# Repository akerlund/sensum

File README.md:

# sensum
Project with many different sensors

Using ChibiOS and so far this is not complete at all.

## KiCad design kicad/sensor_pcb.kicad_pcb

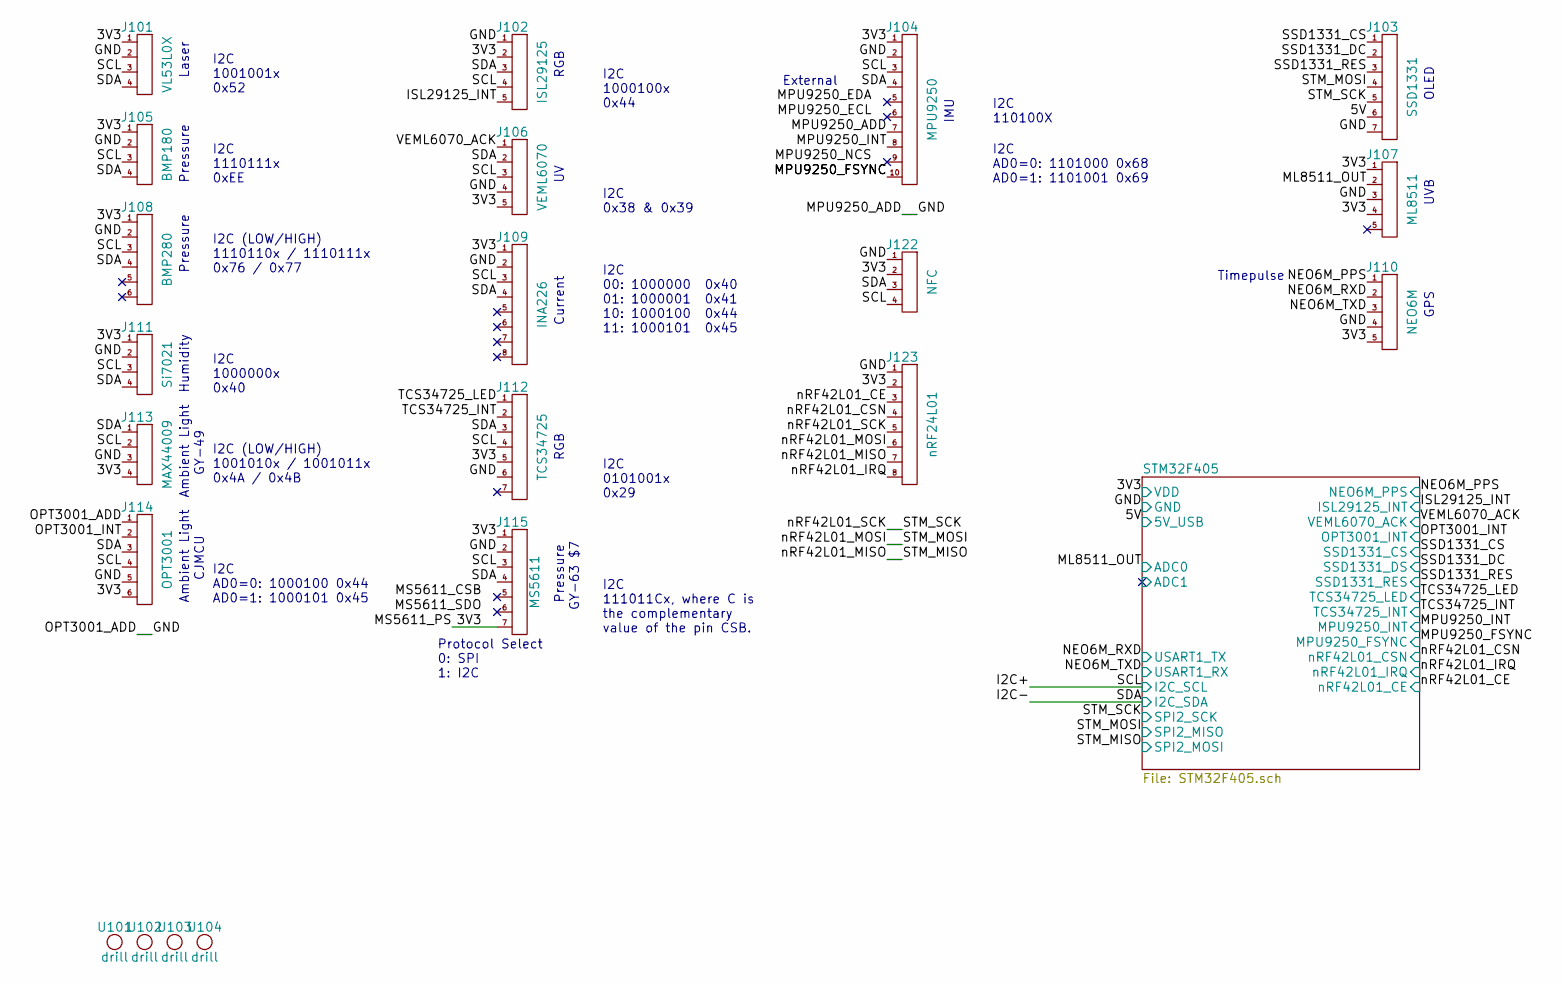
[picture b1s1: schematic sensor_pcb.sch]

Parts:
J101: VL53L0X; pin_socket_4
J102: ISL29125; pin_socket_5
J103: SSD1331; pin_socket_7
J104: MPU9250; pin_socket_10
J105: BMP180; pin_socket_4
J106: VEML6070; pin_socket_5
J107: ML8511; pin_strip_5
J108: BMP280; pin_strip_6
J109: INA226; pin_socket_8
J110: NEO6M; pin_socket_5
J111: Si7021; pin_socket_4
J112: TCS34725; pin_socket_7
J113: MAX44009; pin_socket_4
J114: OPT3001; pin_socket_6
J115: MS5611; pin_socket_7
J122: NFC; pin_socket_4
J123: nRF24L01; pin_socket_4x2
U101, U102, U103, U104: drill; drill_2.0mm

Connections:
/3V3: J101.1, J102.2, J104.1, J105.1, J106.5, J107.1, J107.4, J108.1, J109.1, J110.5, J111.1, J112.5, J113.4, J114.6, J115.1, J115.7, J122.2, J123.2; also elsewhere on the board
/5V: J103.6; also elsewhere on the board
/GND: J101.2, J102.1, J103.7, J104.2, J104.7, J105.2, J106.4, J107.3, J108.2, J109.2, J110.4, J111.2, J112.6, J113.3, J114.1, J114.5, J115.2, J122.1, J123.1; also elsewhere on the board
/I2C+: J101.3, J102.4, J104.3, J105.3, J106.3, J108.3, J109.3, J111.3, J112.4, J113.2, J114.4, J115.3, J122.4; also elsewhere on the board
/I2C-: J101.4, J102.3, J104.4, J105.4, J106.2, J108.4, J109.4, J111.4, J112.3, J113.1, J114.3, J115.4, J122.3; also elsewhere on the board
/ISL29125_INT: J102.5; also elsewhere on the board
/ML8511_OUT: J107.2; also elsewhere on the board
/MPU9250_FSYNC: J104.10; also elsewhere on the board
/MPU9250_INT: J104.8; also elsewhere on the board
/NEO6M_PPS: J110.1; also elsewhere on the board
/NEO6M_RXD: J110.2; also elsewhere on the board
/NEO6M_TXD: J110.3; also elsewhere on the board
/OPT3001_INT: J114.2; also elsewhere on the board
/SSD1331_CS: J103.1; also elsewhere on the board
/SSD1331_DC: J103.2; also elsewhere on the board
/SSD1331_RES: J103.3; also elsewhere on the board
/STM_MISO: J123.7; also elsewhere on the board
/STM_MOSI: J103.4, J123.6; also elsewhere on the board
/STM_SCK: J103.5, J123.5; also elsewhere on the board
/TCS34725_INT: J112.2; also elsewhere on the board
/TCS34725_LED: J112.1; also elsewhere on the board
/VEML6070_ACK: J106.1; also elsewhere on the board
/nRF42L01_CE: J123.3; also elsewhere on the board
/nRF42L01_CSN: J123.4; also elsewhere on the board
/nRF42L01_IRQ: J123.8; also elsewhere on the board

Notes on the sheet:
UVB
Ambient Light
Humidity
GPS
RGB
Current
OLED
Pressure
GY-63 $7
Timepulse
I2C AD0=0: 1000100 0x44 AD0=1: 1000101 0x45
I2C 00: 1000000 0x40 01: 1000001 0x41 10: 1000100 0x44 11: 1000101 0x45
I2C 0x38 & 0x39
Protocol Select 0: SPI 1: I2C
I2C 111011Cx, where C is the complementary value of the pin CSB.
External
I2C 110100X
I2C 1001001x 0x52
I2C 1110111x 0xEE
I2C 1000000x 0x40
Laser
I2C (LOW/HIGH) 1110110x / 1110111x 0x76 / 0x77
I2C (LOW/HIGH) 1001010x / 1001011x 0x4A / 0x4B
I2C 1000100x 0x44
I2C 0101001x 0x29
I2C AD0=0: 1101000 0x68 AD0=1: 1101001 0x69
IMU
GY-49
CJMCU

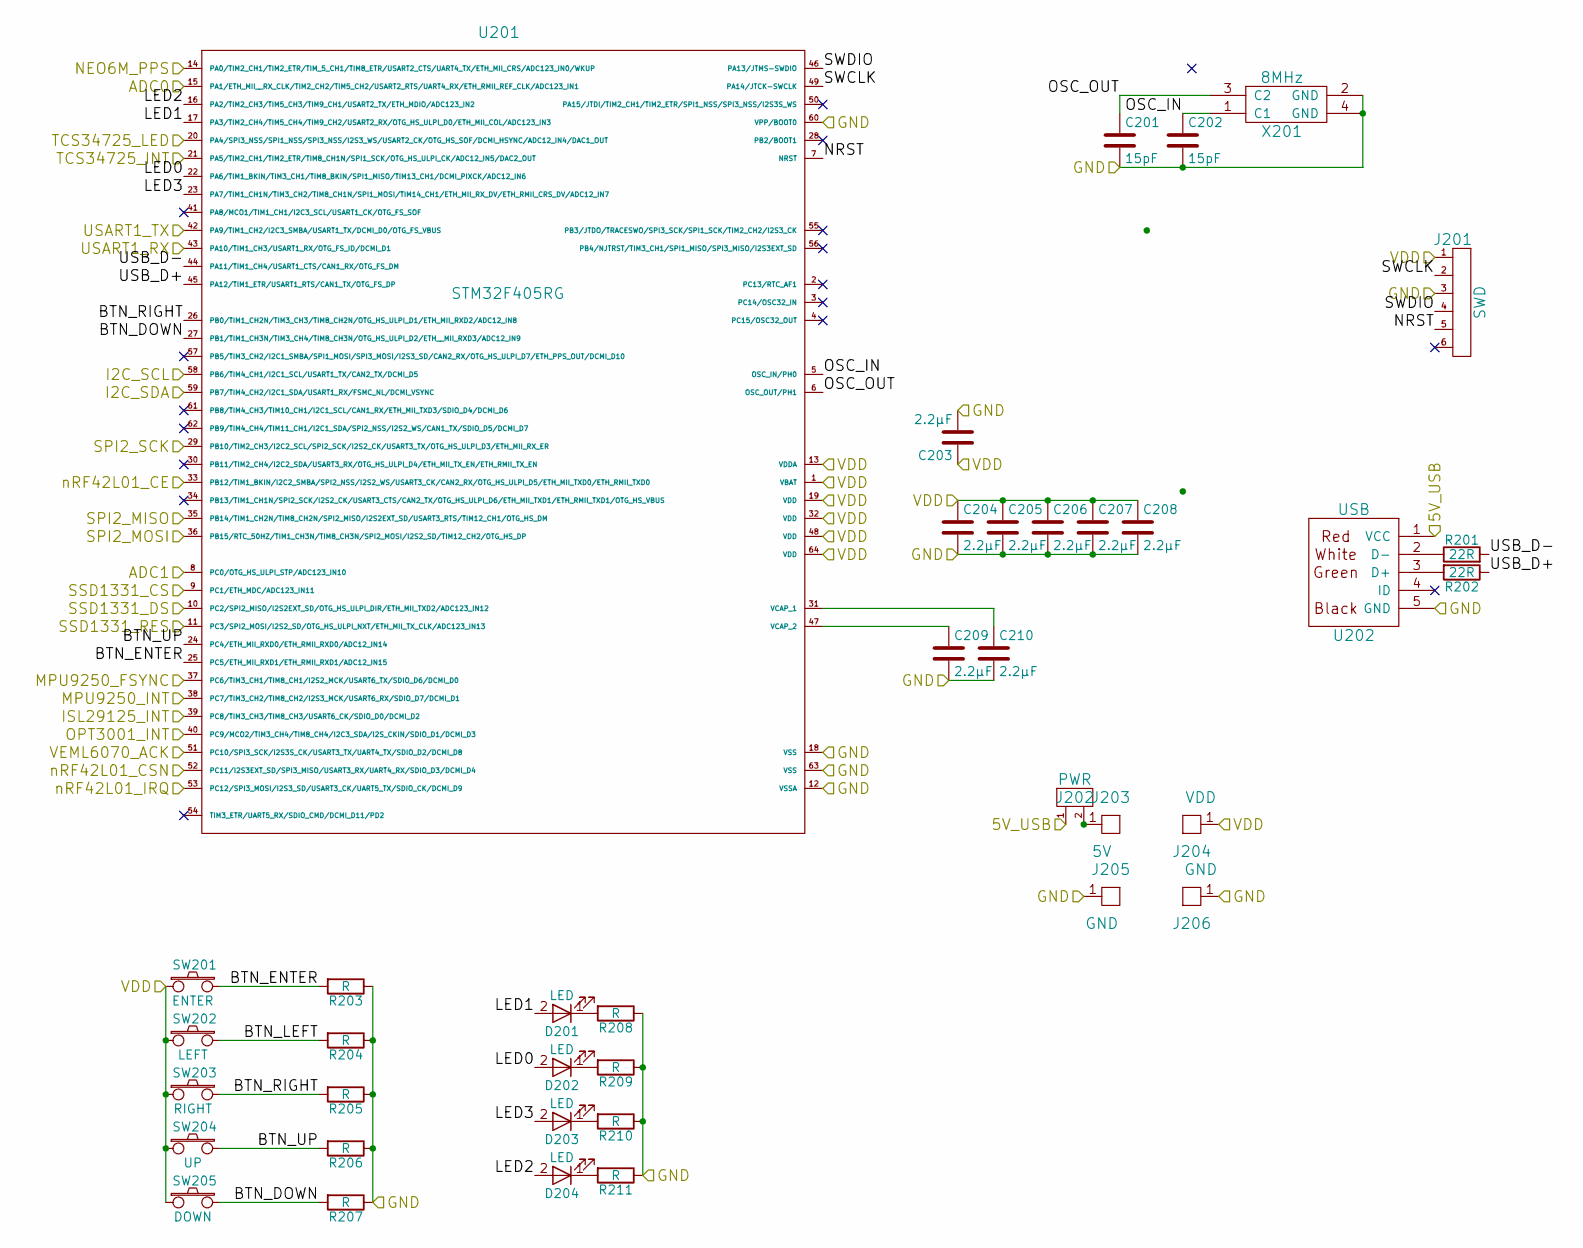
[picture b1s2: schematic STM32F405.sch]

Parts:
C201, C202: 15pF; c_0603
C203, C204, C205, C206, C207, C208, C209, C210: 2.2µF; c_0603
D201, D202, D203, D204: LED; Led_0805
J201: SWD; pin_socket_2mm_6
J202: PWR; pin_socket_2
J203: 5V; pin_socket_1
J204: VDD; pin_socket_1
J205, J206: GND; pin_socket_1
R201, R202: 22R; r_0603
R203, R204, R205, R206, R207, R208, R209, R210, R211: R; r_0603
SW201: ENTER; smd_push
SW202: LEFT; smd_push
SW203: RIGHT; smd_push
SW204: UP; smd_push
SW205: DOWN; smd_push
U201: STM32F405RG; lqfp64
U202: USB; conn_usb_B_mini_smd
X201: 8MHz; Chrystal_3.5x6mm

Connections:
/3V3: C203.1, C204.1, C205.1, C206.1, C207.1, C208.1, J201.1, J204.1, SW201.1, SW202.1, SW203.1, SW204.1, SW205.1, U201.1 (VBAT), U201.13 (VDDA), U201.19 (VDD), U201.32 (VDD), U201.48 (VDD), U201.64 (VDD); also elsewhere on the board
/5V: J202.1, U202.1 (VCC); also elsewhere on the board
/GND: C201.2, C202.2, C203.2, C204.2, C205.2, C206.2, C207.2, C208.2, C209.2, C210.2, J201.3, J205.1, J206.1, R203.1, R204.1, R205.1, R206.1, R207.1, R208.1, R209.1, R210.1, R211.1, U201.12 (VSSA), U201.18 (VSS), U201.60 (VPP/BOOT0), U201.63 (VSS), U202.5 (GND), X201.2 (GND), X201.4 (GND); also elsewhere on the board
/I2C+: U201.58 (PB6/TIM4_CH1/I2C1_SCL/USART1_TX/CAN2_TX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); also elsewhere on the board
/I2C-: U201.59 (PB7/TIM4_CH2/I2C1_SDA/USART1_RX/FSMC_NL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); also elsewhere on the board
/ISL29125_INT: U201.39 (PC8/TIM3_CH3/TIM8_CH3/USART6_CK/SDIO_D0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); also elsewhere on the board
/ML8511_OUT: U201.15 (PA1/ETH_MII__RX_CLK/TIM2_CH2/TIM5_CH2/U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); also elsewhere on the board
/MPU9250_FSYNC: U201.37 (PC6/TIM3_CH1/TIM8_CH1/I2S2_MCK/USART6_T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); also elsewhere on the board
/MPU9250_INT: U201.38 (PC7/TIM3_CH2/TIM8_CH2/I2S3_MCK/USART6_R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); also elsewhere on the board
/NEO6M_PPS: U201.14 (PA0/TIM2_CH1/TIM2_ETR/TIM_5_CH1/TIM8_ET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); also elsewhere on the board
/NEO6M_RXD: U201.42 (PA9/TIM1_CH2/I2C3_SMBA/USART1_TX/DCMI_D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); also elsewhere on the board
/NEO6M_TXD: U201.43 (PA10/TIM1_CH3/USART1_RX/OTG_FS_ID/DCMI_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); also elsewhere on the board
/OPT3001_INT: U201.40 (PC9/MCO2/TIM3_CH4/TIM8_CH4/I2C3_SDA/I2S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); also elsewhere on the board
/SSD1331_CS: U201.9 (PC1/ETH_MDC/ADC123_IN11); also elsewhere on the board
/SSD1331_DC: U201.10 (PC2/SPI2_MISO/I2S2EXT_SD/OTG_HS_ULPI_DI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); also elsewhere on the board
/SSD1331_RES: U201.11 (PC3/SPI2_MOSI/I2S2_SD/OTG_HS_ULPI_NXT/E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); also elsewhere on the board
/STM32F405/BTN_DOWN: R207.2, SW205.2, U201.27 (PB1/TIM1_CH3N/TIM3_CH4/TIM8_CH3N/OTG_HS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)
/STM32F405/BTN_ENTER: R203.2, SW201.2, U201.25 (PC5/ETH_MII_RXD1/ETH_RMII_RXD1/ADC12_IN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)
/STM32F405/BTN_LEFT: R204.2, SW202.2
/STM32F405/BTN_RIGHT: R205.2, SW203.2, U201.26 (PB0/TIM1_CH2N/TIM3_CH3/TIM8_CH2N/OTG_HS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)
/STM32F405/BTN_UP: R206.2, SW204.2, U201.24 (PC4/ETH_MII_RXD0/ETH_RMII_RXD0/ADC12_IN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)
/STM32F405/LED0: D202.2 (A), U201.22 (PA6/TIM1_BKIN/TIM3_CH1/TIM8_BKIN/SPI1_M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)
/STM32F405/LED1: D201.2 (A), U201.17 (PA3/TIM2_CH4/TIM5_CH4/TIM9_CH2/USART2_R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)
/STM32F405/LED2: D204.2 (A), U201.16 (PA2/TIM2_CH3/TIM5_CH3/TIM9_CH1/USART2_T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)
/STM32F405/LED3: D203.2 (A), U201.23 (PA7/TIM1_CH1N/TIM3_CH2/TIM8_CH1N/SPI1_M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)
/STM32F405/NRST: J201.5, U201.7 (NRST)
/STM32F405/OSC_IN: C202.1, U201.5 (OSC_IN/PH0), X201.1 (C1)
/STM32F405/OSC_OUT: C201.1, U201.6 (OSC_OUT/PH1), X201.3 (C2)
/STM32F405/SWCLK: J201.2, U201.49 (PA14/JTCK-SWCLK)
/STM32F405/SWDIO: J201.4, U201.46 (PA13/JTMS-SWDIO)
/STM32F405/USB_D+: R202.1, U201.45 (PA12/TIM1_ETR/USART1_RTS/CAN1_TX/OTG_FS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)
/STM32F405/USB_D-: R201.2, U201.44 (PA11/TIM1_CH4/USART1_CTS/CAN1_RX/OTG_FS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)
/STM_MISO: U201.36 (PB15/RTC_50HZ/TIM1_CH3N/TIM8_CH3N/SPI2_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); also elsewhere on the board
/STM_MOSI: U201.35 (PB14/TIM1_CH2N/TIM8_CH2N/SPI2_MISO/I2S2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); also elsewhere on the board
/STM_SCK: U201.29 (PB10/TIM2_CH3/I2C2_SCL/SPI2_SCK/I2S2_CK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); also elsewhere on the board
/TCS34725_INT: U201.21 (PA5/TIM2_CH1/TIM2_ETR/TIM8_CH1N/SPI1_SC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); also elsewhere on the board
/TCS34725_LED: U201.20 (PA4/SPI3_NSS/SPI1_NSS/SPI3_NSS/I2S3_WS/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); also elsewhere on the board
/VEML6070_ACK: U201.51 (PC10/SPI3_SCK/I2S3S_CK/USART3_TX/UART4_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); also elsewhere on the board
/nRF42L01_CE: U201.33 (PB12/TIM1_BKIN/I2C2_SMBA/SPI2_NSS/I2S2_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); also elsewhere on the board
/nRF42L01_CSN: U201.52 (PC11/I2S3EXT_SD/SPI3_MISO/USART3_RX/UAR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); also elsewhere on the board
/nRF42L01_IRQ: U201.53 (PC12/SPI3_MOSI/I2S3_SD/USART3_CK/UART5_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); also elsewhere on the board
unnamed: C209.1, U201.47 (VCAP_2)
unnamed: C210.1, U201.31 (VCAP_1)
unnamed: D201.1 (K), R208.2
unnamed: D202.1 (K), R209.2
unnamed: D203.1 (K), R210.2
unnamed: D204.1 (K), R211.2
unnamed: J202.2, J203.1
unnamed: R201.1, U202.2 (D-)
unnamed: R202.2, U202.3 (D+)

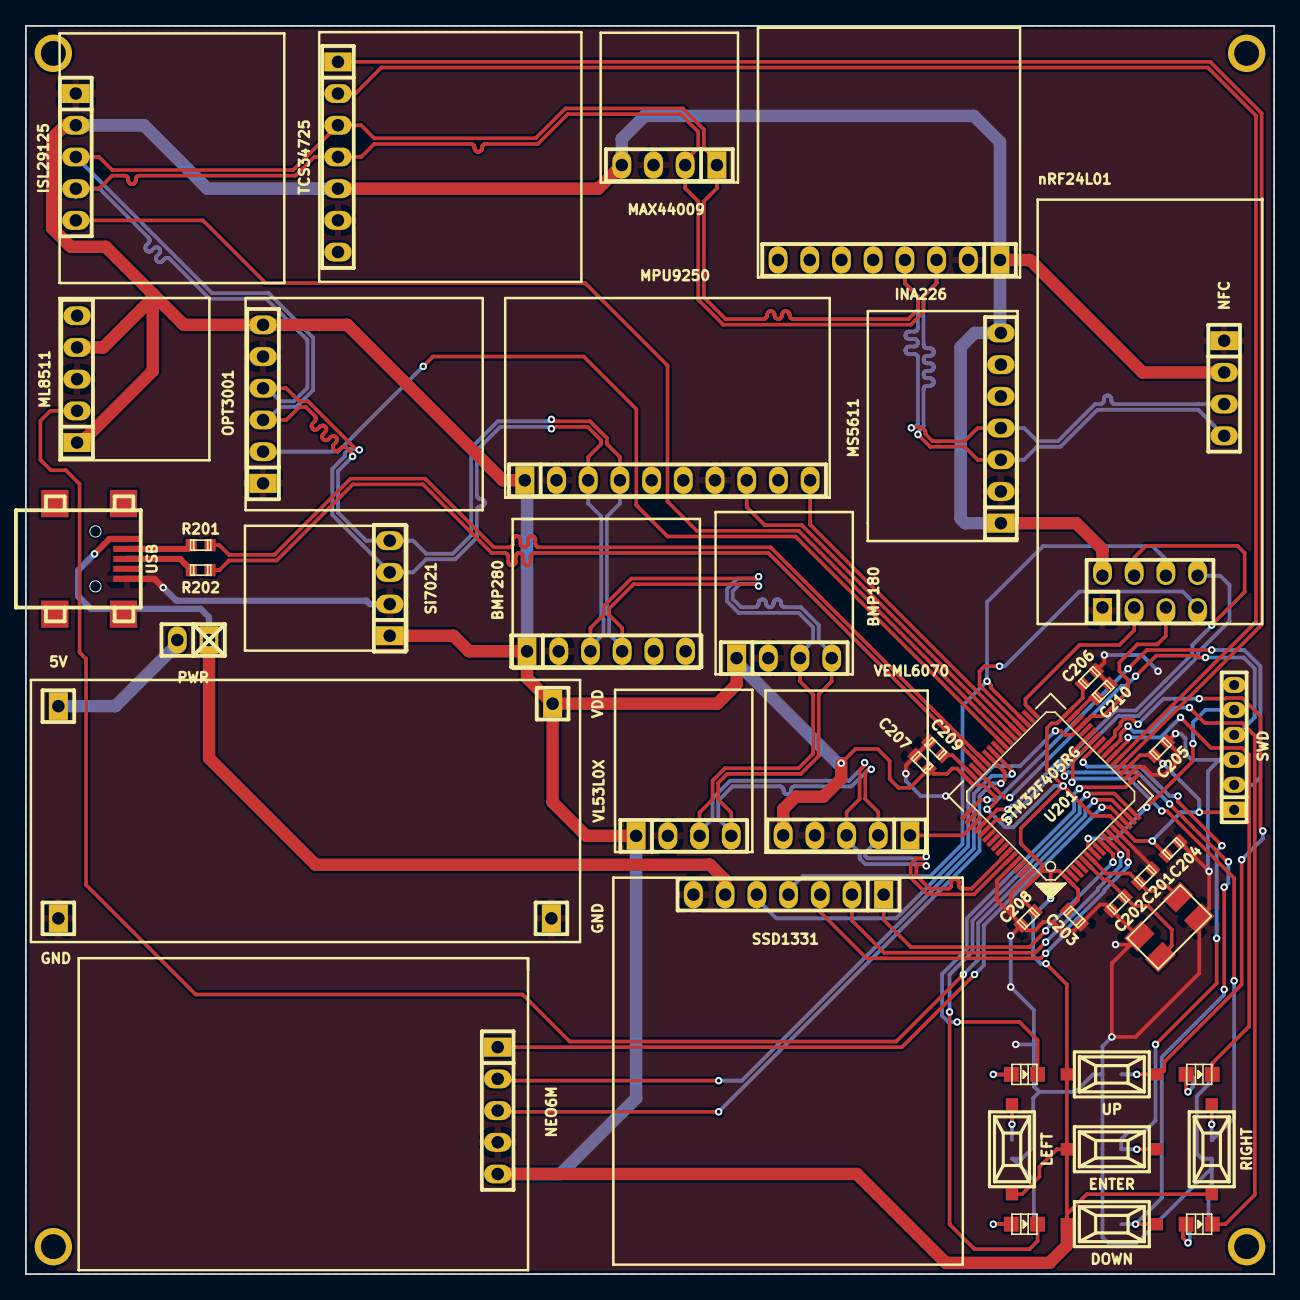
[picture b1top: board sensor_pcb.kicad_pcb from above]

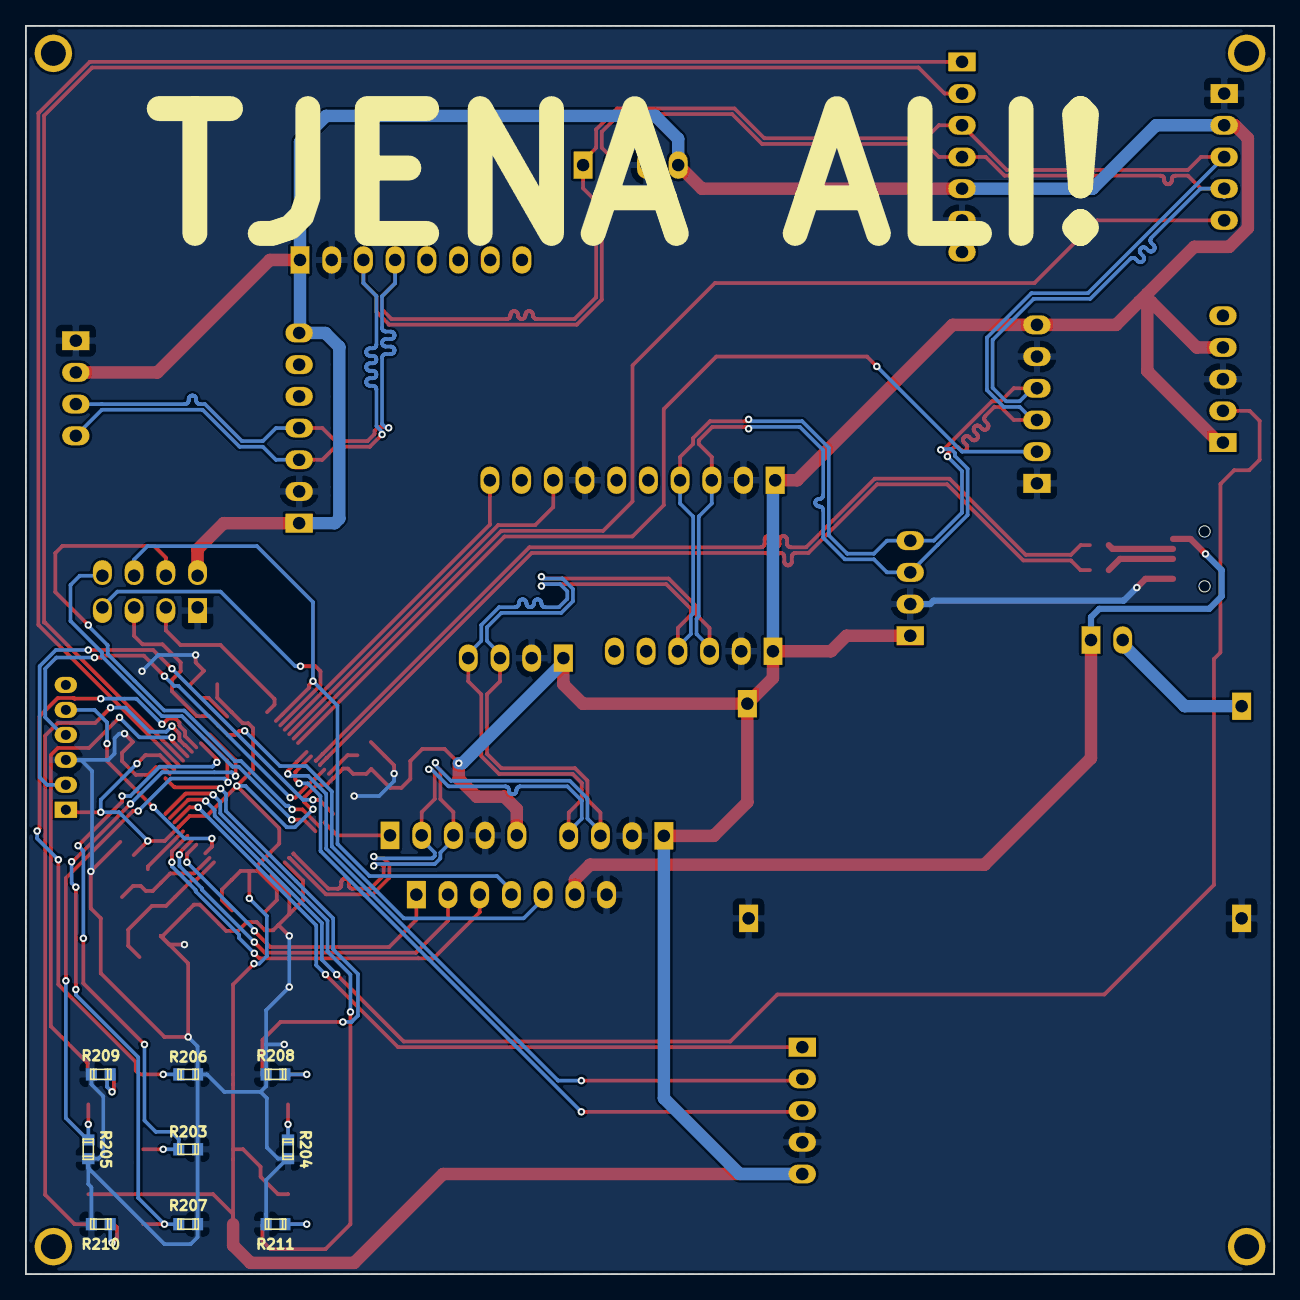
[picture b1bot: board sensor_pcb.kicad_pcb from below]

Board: 2 copper layers, 100.0 x 100.0 mm, 60 parts (9 on the bottom side), 50 nets.

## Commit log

2017-08-06 Basic firmware with coms to GUI
2017-08-09 OLED
2019-12-27 Found this code
2019-12-27 kicad files
2019-12-27 Removed stupid folder in firmware
2019-12-28 Align main, add pic
